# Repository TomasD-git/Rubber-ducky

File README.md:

# Rubber Ducky  

## Small Rubber Ducky, supports standard rubber ducky code, with website interface.  

## Features:  
**Supports standard rubber ducky code**  
**Website interface over wifi**  
**Pretty small**  
**Wifi + Bluetooth**

<details>
<summary>How to make?</summary>
  
First buy PCB, with stencil if u dont trust your soldering skills or without if u do.
then all components in the bom, u can skip solder paste, kapton tape, hot air station if u have these, once arrived 3D print case solder 4 core cable, plug usbc into pc, flash and then just assemble and you are ready.

</details>

<details>
<summary>BOM</summary>

| Name | Purpose | Quantity | Total Cost (USD) | Distributor |
|------|---------|----------|-----------------|-------------|
| [Hot air station](https://www.aliexpress.com/item/1005007009985561.html) | Will solder everything with this | 1 | $39.54 | Aliexpress |
| [PCB + Stencil](https://jlcpcb.com) | All components are on PCB, stencil for easier soldering | 1 | $15.00 | JLCPCB |
| [All components](https://lcsc.com) | All actual components on PCB | Depends on each part | $55.00 | LCSC |
| [4 core cable](https://www.aliexpress.com/item/1005009355432278.html) | Connects the 2 PCBs together | 1 | $4.00 | Aliexpress |
| [Solder paste](https://www.aliexpress.com/item/1005008590694612.html) | Used for soldering | 1 | $7.19 | Aliexpress |
| [Small set of hot air station nozzles](https://www.aliexpress.com/item/1005002724224923.html) | Much easier to solder with 3mm nozzle instead of the 12mm that comes with the hot air station | 1 | $5.18 | Aliexpress |
| [Kapton Tape](https://www.aliexpress.com/item/1005010348863794.html) | Covers soldered stuff so it doesn't get desoldered | 1 | $2.16 | Aliexpress |

**Estimated Total Cost: $128.07**

</details>

## Pictures:

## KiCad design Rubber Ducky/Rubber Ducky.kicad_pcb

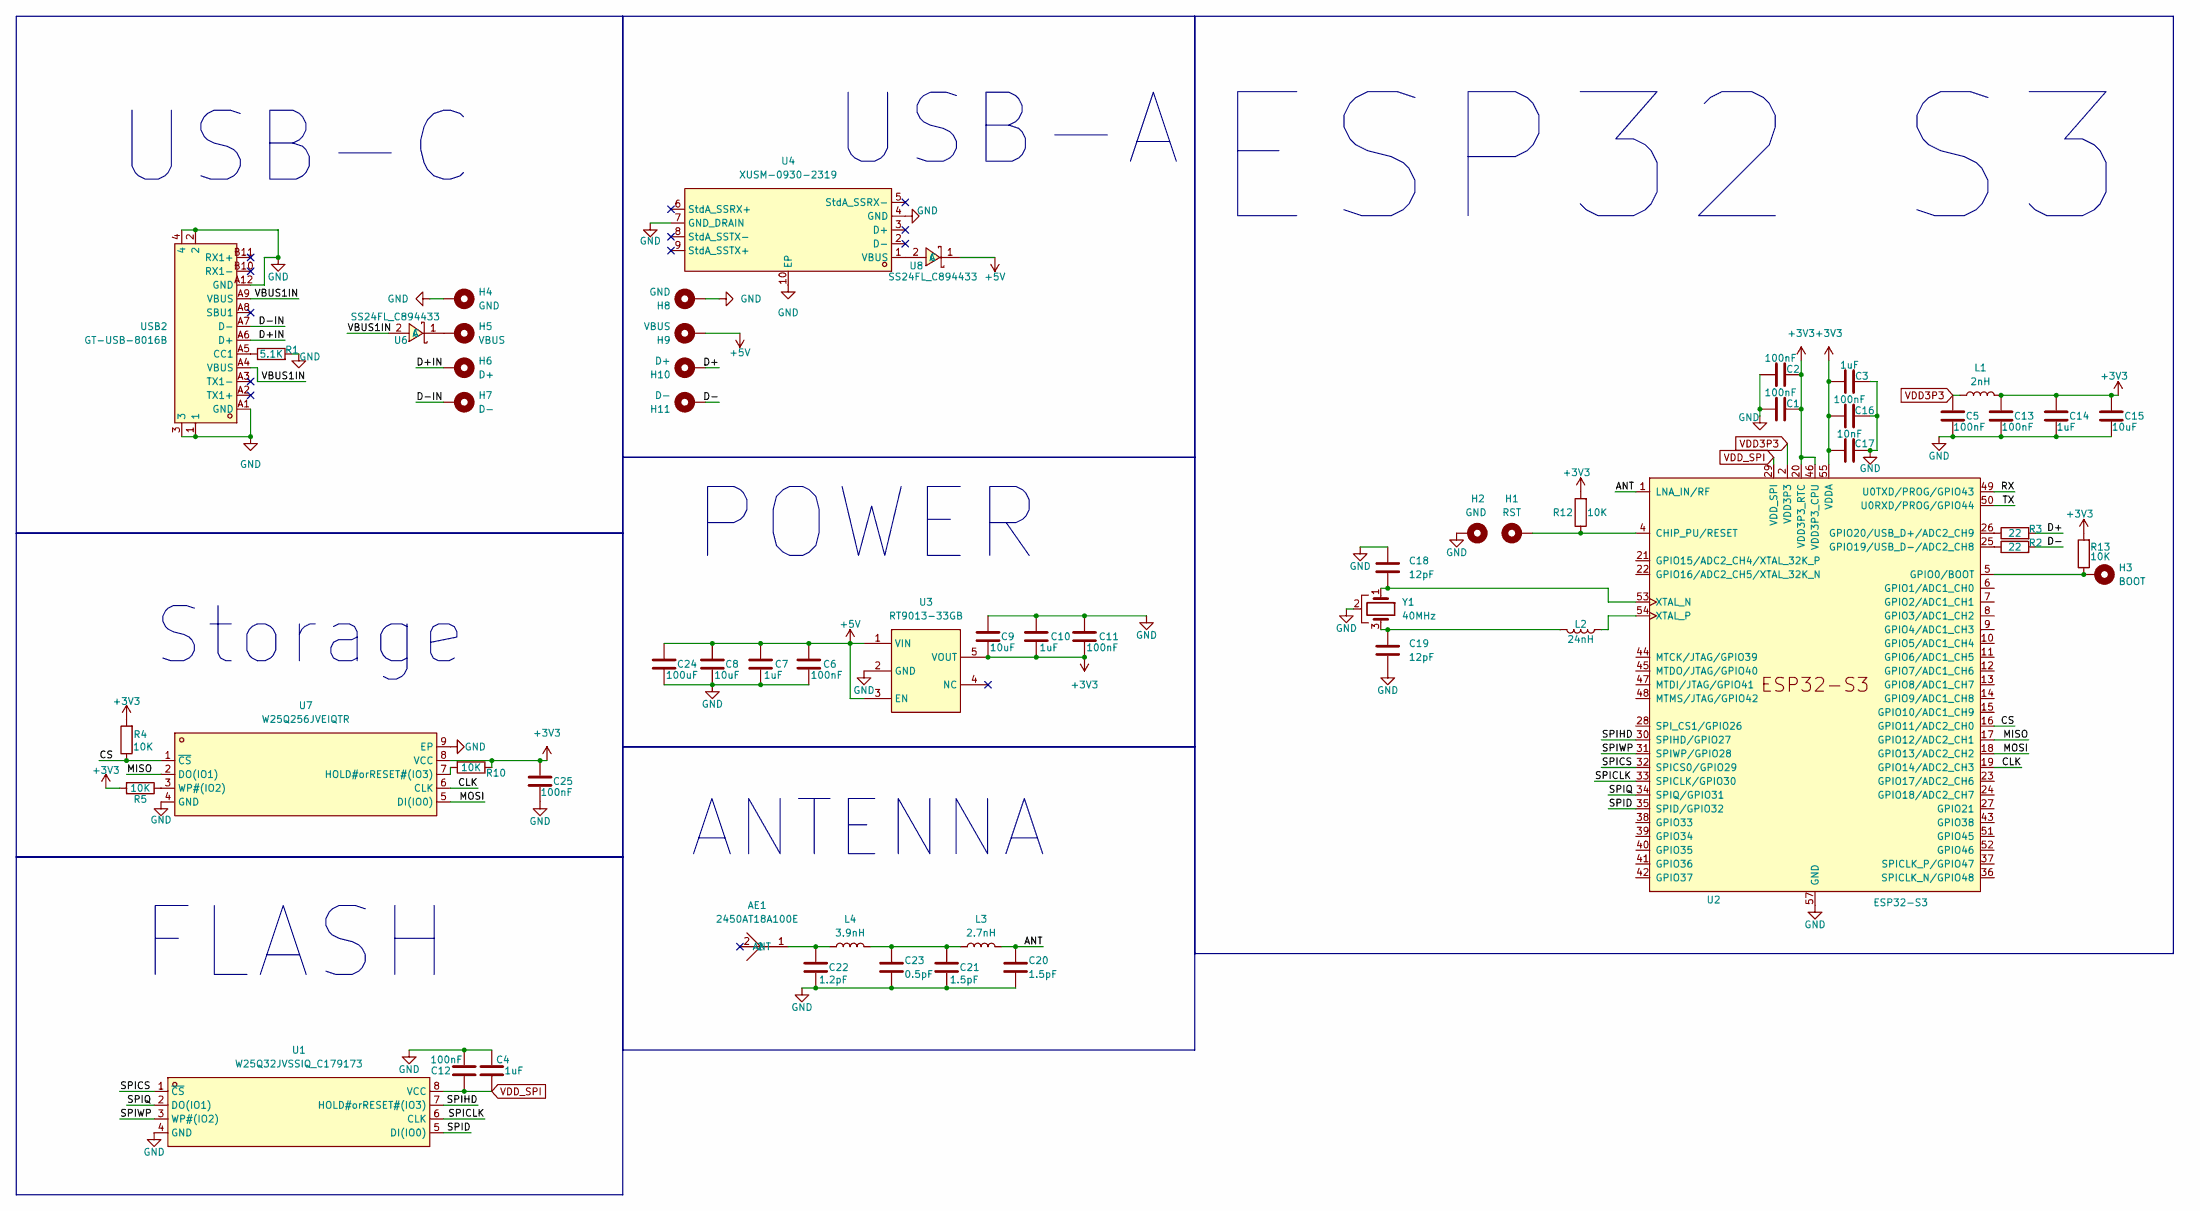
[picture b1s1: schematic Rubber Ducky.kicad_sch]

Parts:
AE1: 2450AT18A100E; ANT-SMD_L3.2-W1.6; MPN 2450AT18A100E; LCSC Part C89334
C1, C2, C5, C6, C11, C12, C13, C16, C25: 100nF; C_0603_1608Metric_Pad1.08x0.95mm_HandSolder
C3, C4, C7: 1uF; C_0805_2012Metric
C8, C9, C15: 10uF; C_1206_3216Metric
C10, C14: 1uF; C_0805_2012Metric_Pad1.18x1.45mm_HandSolder
C17: 10nF; C_0402_1005Metric_Pad0.74x0.62mm_HandSolder
C18, C19: 12pF; C_0402_1005Metric_Pad0.74x0.62mm_HandSolder
C20, C21: 1.5pF; C_0402_1005Metric_Pad0.74x0.62mm_HandSolder
C22: 1.2pF; C_0402_1005Metric_Pad0.74x0.62mm_HandSolder
C23: 0.5pF; C_0402_1005Metric_Pad0.74x0.62mm_HandSolder
C24: 100uF; C_1210_3225Metric
H1: RST; TestPoint_Pad_1.0x1.0mm
H2: GND; TestPoint_Pad_1.0x1.0mm
H3: BOOT; TestPoint_Pad_1.0x1.0mm
H4, H8: GND; PinHeader_1x01_P2.54mm_Vertical
H5, H9: VBUS; PinHeader_1x01_P2.54mm_Vertical
H6, H10: D+; PinHeader_1x01_P2.54mm_Vertical
H7, H11: D-; PinHeader_1x01_P2.54mm_Vertical
L1: 2nH; L_0402_1005Metric_Pad0.77x0.64mm_HandSolder
L2: 24nH; L_0603_1608Metric_Pad1.05x0.95mm_HandSolder
L3: 2.7nH; L_0402_1005Metric_Pad0.77x0.64mm_HandSolder
L4: 3.9nH; L_0402_1005Metric_Pad0.77x0.64mm_HandSolder
R1: 5.1K; R_0805_2012Metric
R2, R3: 22; R_0603_1608Metric_Pad0.98x0.95mm_HandSolder
R4, R5, R10, R12, R13: 10K; R_0805_2012Metric
U1: W25Q32JVSSIQ_C179173; SOIC-8_L5.3-W5.3-P1.27-LS8.0-BL; MPN W25Q32JVSSIQ; LCSC Part C179173
U2: ESP32-S3; QFN-56-1EP_7x7mm_P0.4mm_EP5.6x5.6mm
U3: RT9013-33GB; SOT-23-5_L3.0-W1.7-P0.95-LS2.8-BL; MPN RT9013-33GB; LCSC Part C47773
U4: XUSM-0930-2319; USB-A-SMD_XUSM-0930-2319; MPN XUSM-0930-2319; LCSC Part C7527682
U6, U8: SS24FL_C894433; SOD-123FL_L2.8-W1.8-LS3.6-RD; MPN SS24FL; LCSC Part C894433
U7: W25Q256JVEIQTR; WSON-8_L8.0-W6.10-P1.27-BL-EP; MPN W25Q256JVEIQ; LCSC Part C97522
USB2: GT-USB-8016B; USB-SMD_GT-USB-8016B; MPN GT-USB-8016B; LCSC Part C3001295
Y1: 40MHz; Crystal_SMD_3225-4Pin_3.2x2.5mm_HandSoldering

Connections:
+3V3: C1.2, C2.2, C3.1, C9.2, C10.2, C11.2, C13.1, C14.1, C15.1, C16.1, C17.1, C25.1, L1.2, R4.2, R5.2, R10.1, R12.2, R13.2, U2.20 (VDD3P3_RTC), U2.46 (VDD3P3_CPU), U2.55 (VDDA), U2.56 (VDDA), U3.5 (VOUT), U7.8 (VCC)
+5V: C6.1, C7.1, C8.1, C24.1, H9.1, U3.1 (VIN), U3.3 (EN), U8.1 (C)
/ANT: C20.1, L3.2, U2.1 (LNA_IN/RF)
/CLK: U2.19 (GPIO14/ADC2_CH3), U7.6 (CLK)
/CS: R4.1, U2.16 (GPIO11/ADC2_CH0), U7.1 (~CS)
/D+: H10.1, R3.2
/D+IN: H6.1, USB2.A6 (D+)
/D-: H11.1, R2.2
/D-IN: H7.1, USB2.A7 (D-)
/MISO: U2.17 (GPIO12/ADC2_CH1), U7.2 (DO(IO1))
/MOSI: U2.18 (GPIO13/ADC2_CH2), U7.5 (DI(IO0))
/RX: U2.49 (U0TXD/PROG/GPIO43)
/SPICLK: U1.6 (CLK), U2.33 (SPICLK/GPIO30)
/SPICS: U1.1 (~CS), U2.32 (SPICS0/GPIO29)
/SPID: U1.5 (DI(IO0)), U2.35 (SPID/GPIO32)
/SPIHD: U1.7 (HOLD#orRESET#(IO3)), U2.30 (SPIHD/GPIO27)
/SPIQ: U1.2 (DO(IO1)), U2.34 (SPIQ/GPIO31)
/SPIWP: U1.3 (WP#(IO2)), U2.31 (SPIWP/GPIO28)
/TX: U2.50 (U0RXD/PROG/GPIO44)
/VBUS1IN: U6.2 (A), USB2.A4 (VBUS), USB2.A9 (VBUS)
GND: C1.1, C2.1, C3.2, C4.2, C5.2, C6.2, C7.2, C8.2, C9.1, C10.1, C11.1, C12.2, C13.2, C14.2, C15.2, C16.2, C17.2, C18.1, C19.2, C20.2, C21.2, C22.2, C23.2, C24.2, C25.2, H2.1, H4.1, H8.1, R1.2, U1.4 (GND), U2.57 (GND), U3.2 (GND), U4.4 (GND), U4.7 (GND_DRAIN), U4.10 (EP), U7.4 (GND), U7.9 (EP), USB2.1, USB2.2, USB2.3, USB2.4, USB2.A1 (GND), USB2.A12 (GND), Y1.2
unnamed: AE1.1 (ANT), C22.1, L4.1
unnamed: C19.1, L2.2, Y1.3
unnamed: C21.1, C23.1, L3.1, L4.2
unnamed: H1.1, R12.1, U2.4 (CHIP_PU/RESET)
unnamed: H3.1, R13.1, U2.5 (GPIO0/BOOT)
unnamed: R2.1, U2.25 (GPIO19/USB_D-/ADC2_CH8)
unnamed: R3.1, U2.26 (GPIO20/USB_D+/ADC2_CH9)
unnamed: C18.2, U2.53 (XTAL_N), Y1.1
unnamed: L2.1, U2.54 (XTAL_P)
unnamed: U4.1 (VBUS), U8.2 (A)
unnamed: H5.1, U6.1 (C)
unnamed: R10.2, U7.7 (HOLD#orRESET#(IO3))
unnamed: R5.1, U7.3 (WP#(IO2))
unnamed: R1.1, USB2.A5 (CC1)
VDD3P3: C5.1, L1.1, U2.2 (VDD3P3), U2.3 (VDD3P3)
VDD_SPI: C4.1, C12.1, U1.8 (VCC), U2.29 (VDD_SPI)

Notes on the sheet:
Storage
ANTENNA
USB-C
POWER
ESP32 S3
USB-A
FLASH

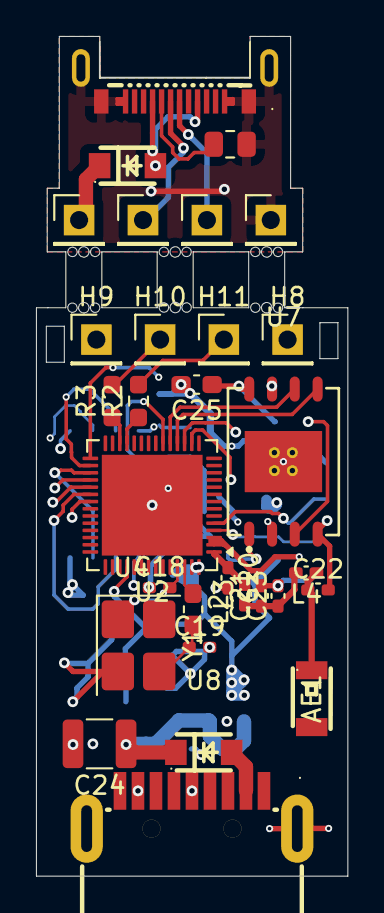
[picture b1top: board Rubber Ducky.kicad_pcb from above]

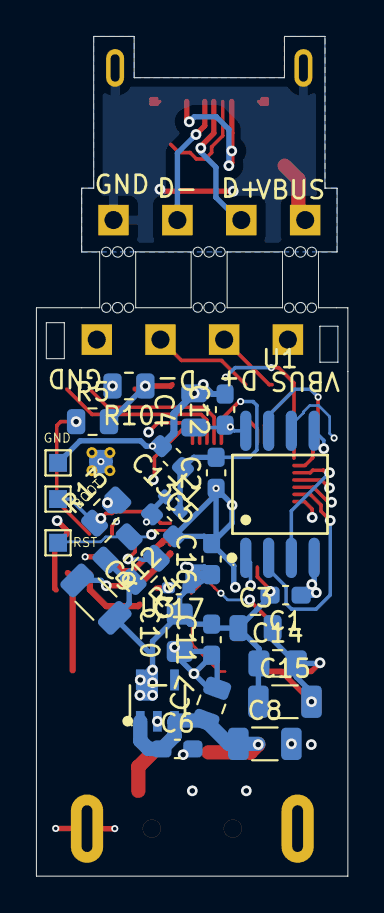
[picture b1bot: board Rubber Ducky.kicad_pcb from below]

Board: 4 copper layers, 17.3 x 46.6 mm, 58 parts (28 on the bottom side), 35 nets.

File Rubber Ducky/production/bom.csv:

Designator,Footprint,Quantity,Value,LCSC Part #
AE1,ANT-SMD_L3.2-W1.6,1,2450AT18A100E,C89334
"C1, C11, C12, C13, C16, C2, C25, C5, C6",0603,9,100nF,
"C10, C14, C3, C4, C7",0805,5,1uF,
"C15, C8, C9",1206,3,10uF,
C17,0402,1,10nF,
"C18, C19",0402,2,12pF,
"C20, C21",0402,2,1.5pF,
C22,0402,1,1.2pF,
C23,0402,1,0.5pF,
C24,1210,1,100uF,
L1,0402,1,2nH,
L2,0603,1,24nH,
L3,0402,1,2.7nH,
L4,0402,1,3.9nH,
R1,0805,1,5.1K,
"R10, R12, R13, R4, R5",0805,5,10K,
"R2, R3",0603,2,22,
U1,SOIC-8_L5.3-W5.3-P1.27-LS8.0-BL,1,W25Q32JVSSIQ_C179173,C179173
U2,QFN-56-1EP_7x7mm_P0.4mm_EP5.6x5.6mm,1,ESP32-S3,
U3,SOT-23-5_L3.0-W1.7-P0.95-LS2.8-BL,1,RT9013-33GB,C47773
U4,USB-A-SMD_XUSM-0930-2319,1,XUSM-0930-2319,C7527682
"U6, U8",SOD-123FL_L2.8-W1.8-LS3.6-RD,2,SS24FL_C894433,C894433
U7,WSON-8_L8.0-W6.10-P1.27-BL-EP,1,W25Q256JVEIQTR,C97522
USB2,USB-SMD_GT-USB-8016B,1,GT-USB-8016B,C3001295
Y1,Crystal_SMD_3225-4Pin_3.2x2.5mm_HandSoldering,1,40MHz,

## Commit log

2026-06-05 added firmware files
2026-06-05 added CAD files
2026-06-05 added PCB/KiCad files
2026-06-05 Enhance README with detailed description and images
    Expanded the README to include features and images.
2026-06-07 added production files
2026-06-07 added BOM
2026-06-07 Update README with assembly instructions and BOM
    Added detailed instructions for assembly and a bill of materials (BOM) with estimated costs.
